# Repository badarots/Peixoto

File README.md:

#

## Afazeres

Controle

- [x] Agendamento
- [x] Inicialização com systemd
- [x] Log
- [x] Banco de dados
- [x] Informar status aos clientes
- [x] Controle de velocidade do tratador
- [ ] Desabilitar temporizador externo
- [ ] Refazer agenda do tratador
- [ ] Reformular configurações

WAMP

- [x] Estabelecer comunicação
- [x] Definir rota de conexão
- [x] Processamento de mensagens
- [x] Autenticação
- [ ] Criptografia

MQTT

- [ ] Autenticação e autorizações
- [ ] Criptografia
- [ ] QoS

## Configuração do Raspiberry

### Atualização e instalação de pacotes necessários

    sudo apt update && sudo apt upgrade
    sudo apt install git mosquitto

Pacotes úteis:

    sudo apt install wiringpi sqlite3 nmap

### Instalando interpretador python dedicado (3.6)

Pacotes necessários

    sudo apt-get -y install build-essential libssl-dev libffi-dev libreadline-dev libbz2-dev libsqlite3-dev libncurses5-dev

Instalação

    cd $HOME
    wget https://www.python.org/ftp/python/3.6.6/Python-3.6.6.tar.xz
    tar xvf Python-3.6.6.tar.xz
    cd Python-3.6.6 && ./configure --prefix=$HOME/python366
    make && make install
    sudo ln -s ~/python366/bin/python3 /usr/local/bin/pythond
    sudo ln -s ~/python366/bin/pip /usr/local/bin/pipd

Instalando e atualizando pip

    pythond -m ensurepip
    pythond -m pip install -U pip

### Instalando pypy (não está funcionando)

Pacotes necessários:

    sudo apt install libssl-dev libffi-dev

Instalação:

    wget https://bitbucket.org/pypy/pypy/downloads/pypy3-v6.0.0-linux-armhf-raspbian.tar.bz2
    sudo mkdir /opt/pypy
    sudo tar xvf pypy3-v6.0.0-linux-armhf-raspbian.tar.bz2 --directory /opt/pypy/ --strip-components=1
    sudo ln -s /opt/pypy/bin/pypy3 /usr/local/bin/pypy

Intalando pip

    pypy -m ensurepip
    pypy -m pip install -U pip

[referencia](https://github.com/Nikolay-Kha/PyCNC/issues/20)

### PlatformIO no raspberry

Requisito: python 2.7

Adcione o usuario ao grupo 'dialout'

    sudo usermod -a -G dialout pi

Habilite a comunicação serial

    raspi-config

Interfacing -> Serial

Configure o arquivo 99-platformio-udev.rules

    curl -fsSL https://raw.githubusercontent.com/platformio/platformio-core/develop/scripts/99-platformio-udev.rules | sudo tee /etc/udev/rules.d/99-platformio-udev.rules
    sudo service udev restart

Script de instalaçao do platformio (também instala pip)

    sudo python -c "$(curl -fsSL https://raw.githubusercontent.com/platformio/platformio/develop/scripts/get-platformio.py)"

## Instalação

Clone o repositório na pasta home

    cd $HOME
    git clone https://github.com/badarot/Peixoto

Dentro da pasta criada instale as dependências

    cd Peixoto
    pipd install -r requeriments-server.txt

Se pretente usar um broker WAMP remoto basta instalar as dependências de ``requiriments.txt``.

### Inicialização manual

Inicialize o ``crossbar`` e rode o script ``peixoto.py`` com o interpretador python dedicado. WAMP

    cd Peixoto
    crossbar start &
    pythond peixoto.py

### Opções

Para rodar em modo de teste (sem o controle dos GPIOs) use o argumento ``teste``

    pythond peixoto.py teste

Para se conectar em um broker WAMP remoto use o argumento ``remoto``.

    pythond peixoto.py remoto

### Inicialização automática

Para habilitar a inicialização automática do crossbar e do peixoto copie os arquivos ``crossbar.service`` e ``peixoto.service`` dentro da pasta ``services`` para:

> /etc/systemd/system/

E execute:

    sudo systemctl enable crossbar && sudo systemctl start crossbar
    sudo systemctl enable peixoto && sudo systemctl start peixoto

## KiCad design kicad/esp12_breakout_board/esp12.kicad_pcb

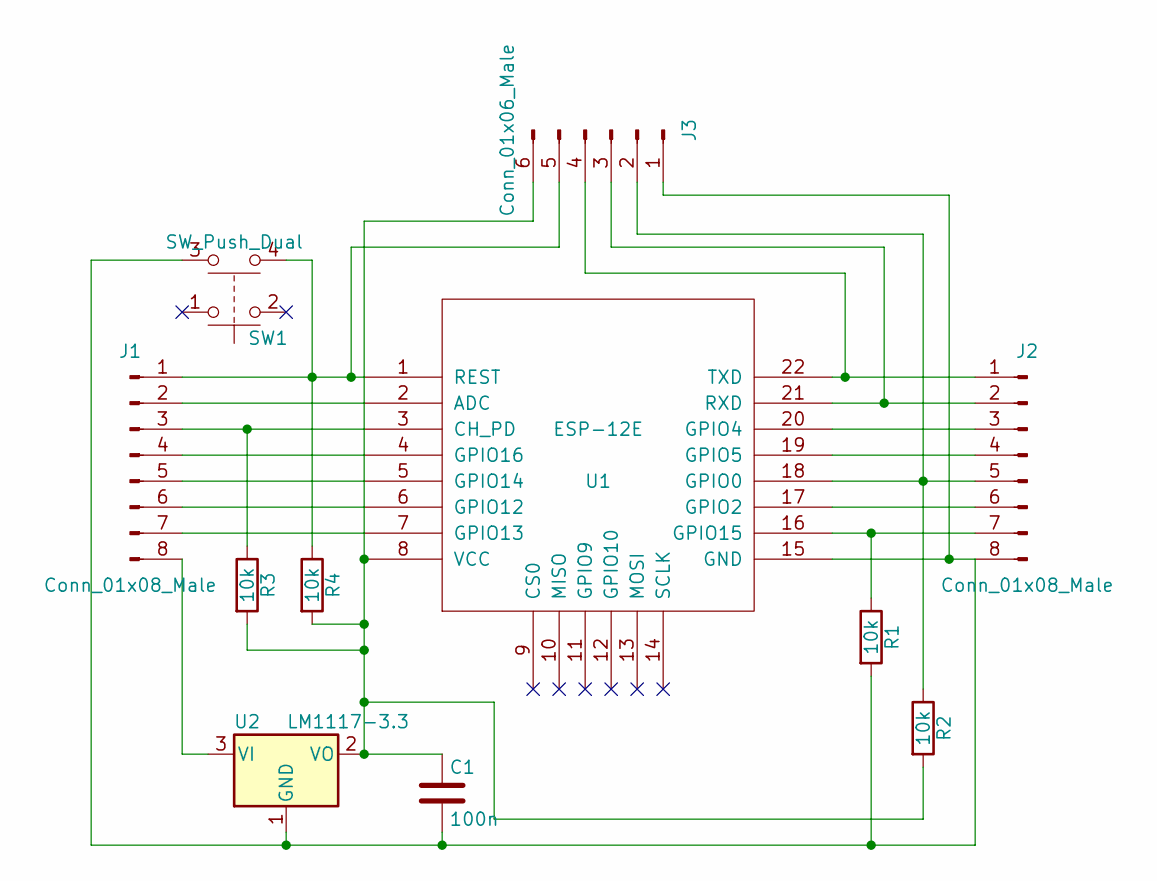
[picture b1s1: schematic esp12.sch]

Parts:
C1: 100n; C_Disc_D4.7mm_W2.5mm_P5.00mm
J1, J2: Conn_01x08_Male; Pin_Header_Straight_1x08_Pitch2.54mm
J3: Conn_01x06_Male; Pin_Header_Straight_1x06_Pitch2.54mm
R1, R2, R3, R4: 10k; R_Axial_DIN0204_L3.6mm_D1.6mm_P7.62mm_Horizontal
SW1: SW_Push_Dual; SW_TH_Tactile_Omron_B3F-10xx
U1: ESP-12E
U2: LM1117-3.3; SOT-223

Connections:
unnamed: C1.1, J3.6, R2.2, R3.2, R4.2, U1.8 (VCC), U2.2 (VO)
unnamed: C1.2, J2.8, J3.1, R1.2, SW1.3, U1.15 (GND), U2.1 (GND)
unnamed: J1.1, J3.5, R4.1, SW1.4, U1.1 (REST)
unnamed: J1.2, U1.2 (ADC)
unnamed: J1.3, R3.1, U1.3 (CH_PD)
unnamed: J1.4, U1.4 (GPIO16)
unnamed: J1.5, U1.5 (GPIO14)
unnamed: J1.6, U1.6 (GPIO12)
unnamed: J1.7, U1.7 (GPIO13)
unnamed: J1.8, U2.3 (VI)
unnamed: J2.1, J3.4, U1.22 (TXD)
unnamed: J2.2, J3.3, U1.21 (RXD)
unnamed: J2.3, U1.20 (GPIO4)
unnamed: J2.4, U1.19 (GPIO5)
unnamed: J2.5, J3.2, R2.1, U1.18 (GPIO0)
unnamed: J2.6, U1.17 (GPIO2)
unnamed: J2.7, R1.1, U1.16 (GPIO15)

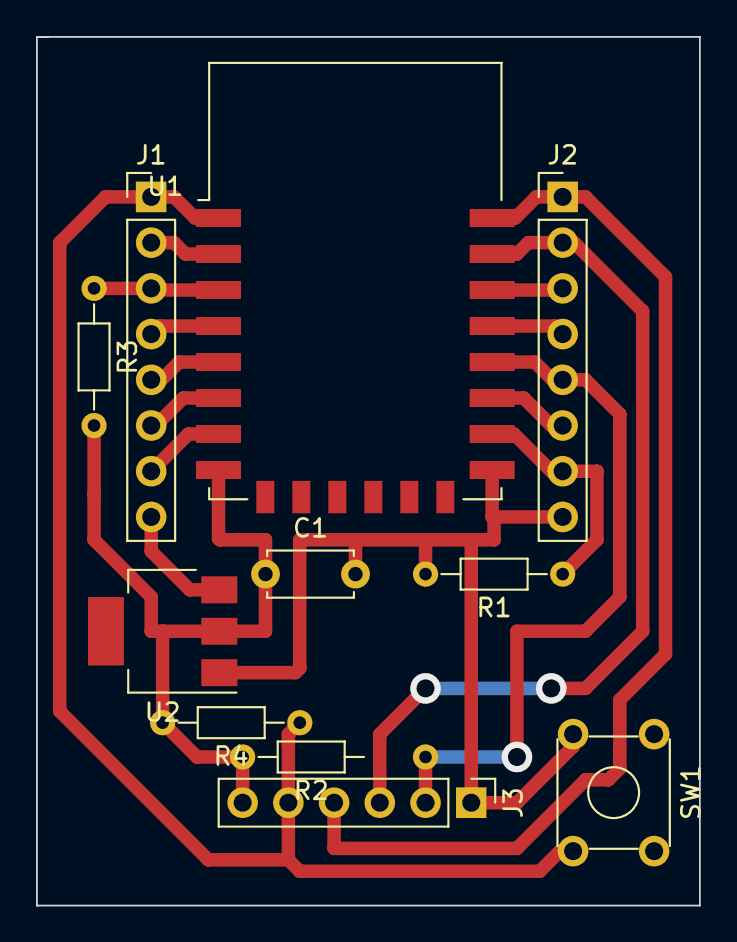
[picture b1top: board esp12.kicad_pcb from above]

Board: 2 copper layers, 36.8 x 48.3 mm, 11 parts (0 on the bottom side), 17 nets.

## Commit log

2018-06-16 Início
    Nesse primeiro commit está implementado o site com as funcionalidades básicas. O cliente interpreta as mensagens recebidas e controla o aerador.
2018-06-19 Uma série de pequenas mudança
2018-06-19 Mais modificações para integração com o raspi
2018-06-19 Adcionada lista de afazeres
2018-06-20 Log funcionando
2018-06-20 Mudando diretório de log
2018-06-20 Download remoto do JQuery
2018-06-20 Cabeçalhos de formulários não são mais removidos
2018-06-22 Adcionado banco de dados e reorganização do cógido
2018-06-23 sava agenda e reorganiçao do banco de dados
2018-06-23 Site recupera agenda
2018-06-24 autenticação implementada
2018-06-24 login no site
2018-06-24 Novo caminhos para a pasta de dados
2018-06-24 Caminho absoluto para a pasta de dados
2018-06-24 mensagem de status mais suscinta
2018-06-24 site: ajustado para celulares
2018-06-26 Site: único arquivo para a agenda
2018-07-06 kicad: placas para esp12 e conectores
2018-07-06 botao de reset na placa do esp12
2018-07-06 kicad: algumas mudanças
2018-07-10 Primeiros passos para utilização
2018-07-13 Mudanças nas pcis
2018-07-14 Adcionado ativadores
2018-07-14 arrumação
2018-07-14 teste2
2018-07-14 finalmente
2018-07-14 finalmente2
2018-07-15 site: ativar
2018-07-16 "adcionado interruptores"
    falta a função de atualizar o estado dos interruptores quando outro
    clientes os mudam
2018-07-16 problema com nome de registros
2018-07-23 componente adcionado: esp12 para o tratador
2018-07-25 adcionado suporte aos componentes remotos
2018-07-25 correções nas msg dos componentes
2018-07-27 alguns consertos
2018-08-03 Correção no caminho da pasta de trabalho
2018-08-05 componentes movidos para outro repositório
2018-08-07 Adcionado suporte para MQTT
2018-08-07 Novo mopeamento de pinos
2018-08-07 Novo mapeamento de pinos
2018-08-07 Correção de bug
2018-08-07 Correções
2018-08-07 Adcionado controle do tratador
2018-08-07 Adcionalo cotrole do tratador
2018-08-08 Leitura do sensor dht
2018-08-09 Banco de dados para o sensor dht
2018-08-09 dht lido a cada meia hora
2018-08-11 Mudanças da leitura do dht e conversão da freq. do motor
2018-08-14 Envio dos dados do sensor dht
2018-08-14 Site removido
2018-08-14 Site adcionado como submódulo
2018-08-16 Preparando merge
2018-08-16 README atualizado
2018-08-17 Controle dos temp. externos
2018-08-18 Revertendo "Controle dos temp. externos"
    This reverts commit 07ced212013ead3d817ef0d48166314804e39e7b.
2018-08-20 Retirando a classe Controlraspi
2018-08-20 Erro revertido, porta do crossbar alterada indevidamente
2018-08-20 Método stop fecha todas as conexões
2018-09-04 Versão utilizando asyncio como framework para programação assincrona
